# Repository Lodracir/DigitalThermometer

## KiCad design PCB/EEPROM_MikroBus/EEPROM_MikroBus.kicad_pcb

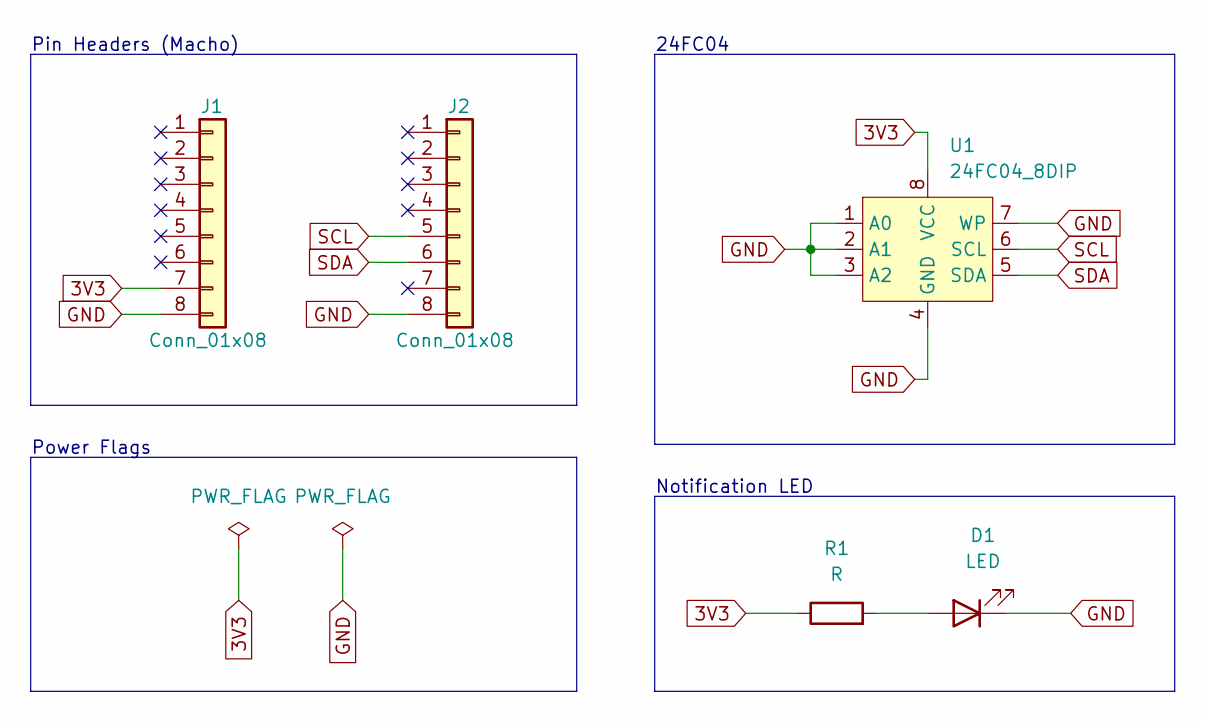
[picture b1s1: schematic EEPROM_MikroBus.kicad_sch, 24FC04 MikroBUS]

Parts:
D1: LED; LED_0603_1608Metric_Pad1.05x0.95mm_HandSolder
J1, J2: Conn_01x08; PinHeader_1x08_P2.54mm_Vertical
R1: R; R_0603_1608Metric_Pad0.98x0.95mm_HandSolder
U1: 24FC04_8DIP; DIP-8_W7.62mm_Socket

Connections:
3V3: J1.7, R1.1, U1.8 (VCC)
GND: D1.1 (K), J1.8, J2.8, U1.1 (A0), U1.2 (A1), U1.3 (A2), U1.4 (GND), U1.7 (WP)
unnamed: D1.2 (A), R1.2
SCL: J2.5, U1.6 (SCL)
SDA: J2.6, U1.5 (SDA)

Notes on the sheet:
Power Flags
Notification LED
24FC04
Pin Headers (Macho)

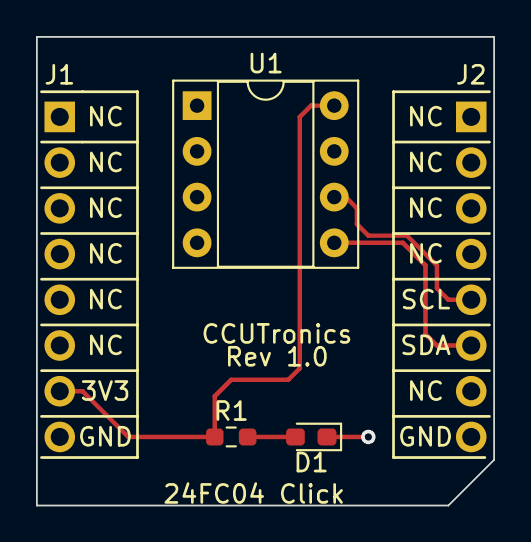
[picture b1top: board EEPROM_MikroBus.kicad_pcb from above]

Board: 2 copper layers, 25.4 x 26.0 mm, 5 parts (0 on the bottom side), 5 nets.

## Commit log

2022-07-12 Added Readme file
2022-08-02 Initial Commit (Added MCU Files)
2022-08-03 Added EEPROM Files
2022-08-03 Fixed possible bugs to GPIO Driver
2022-08-17 Added TIM2 Driver
2022-08-19 Modified EEPROM files for I2C Mem
2022-08-19 Test 1: 8bit data write/read
2022-08-19 EEPROM Library completed (V1.0)
2022-08-19 Added MikroBUS PCB Files
2022-08-22 Added EEPROM PCB Files (Complete)
2022-08-22 Improvements after merge
2022-08-24 Minor Corrections
2022-08-24 Auto stash before merge of "main" and "origin/main"
2022-08-25 State Machine added (v0.1)
2022-10-11 Added UART Driver
2022-10-27 Added Buffer files, improvements on drivers
2022-10-27 Added Custom UART Driver
2022-10-27 Serial Library created, AppMain files header
2023-03-02 SerialComm rework, additional added files.
    Added CircularBuffer files, SerialComm module reworked, some clean up.
